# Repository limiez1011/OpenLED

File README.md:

# OpenLED

Open source ws2812 LED strips in 3 different size and connector configurations.

# Variants

There are 3 variants for the OpenLED:

- OpenLED LONG
- OpenLED WIDE
- OpenLED COMPACT

# Variant info and BOM's

## OpenLED LONG

- Dimensions: 44.2x7.1x7* (LxWxH)(mm) *Estimated

**BOM (per piece)**
|   | NAME                      | PURPOSE       | QTY | PRICE (MOQ)                  | LINK                                                      |
|---|---------------------------|---------------|-----|------------------------------|-----------------------------------------------------------|
| 1 | JST SM03B-SRSS-TB(LF)(SN) | JST Connector | 2   | $0.98                        | [LINK](https://www.lcsc.com/product-detail/C160403.html)  |
| 2 | Worldsemi WS2812B-V5/W    | LED'S         | 4   | $0.55                        | [LINK](https://www.lcsc.com/product-detail/C2874885.html) |
| 3 | YAGEO CC0402KRX7R9BB104   | Decoupling    | 4   | $0.5                         | [LINK](https://www.lcsc.com/product-detail/C131394.html)  |
|   | PCB                       | PCB           | 1   | Varies                       | [LINK](https://jlcpcb.com)                                |
|   | Total                     |               |     | $2.03 + PCB + SHIPPING/TAXES |                                                           |

- Photos

## OpenLED WIDE

- Dimensions: 40.1x8x7* (LxWxH)(mm) *Estimated

**BOM (per piece)**
|   | NAME                      | PURPOSE       | QTY | PRICE (MOQ)                  | LINK                                                      |
|---|---------------------------|---------------|-----|------------------------------|-----------------------------------------------------------|
| 1 | JST SM03B-SRSS-TB(LF)(SN) | JST Connector | 2   | $0.98                        | [LINK](https://www.lcsc.com/product-detail/C160403.html)  |
| 2 | Worldsemi WS2812B-V5/W    | LED'S         | 4   | $0.55                        | [LINK](https://www.lcsc.com/product-detail/C2874885.html) |
| 3 | YAGEO CC0402KRX7R9BB104   | Decoupling    | 4   | $0.5                         | [LINK](https://www.lcsc.com/product-detail/C131394.html)  |
|   | PCB                       | PCB           | 1   | Varies                       | [LINK](https://jlcpcb.com)                                |
|   | Total                     |               |     | $2.03 + PCB + SHIPPING/TAXES |                                                           |

- Photos

## OpenLED COMPACT

- Dimensions: 31.8x7.1x7* (LxWxH)(mm) *Estimated

**BOM (per piece)**
|   | NAME                      | PURPOSE       | QTY | PRICE (MOQ)                  | LINK                                                      |
|---|---------------------------|---------------|-----|------------------------------|-----------------------------------------------------------|
| 1 | Worldsemi WS2812B-V5/W    | LED'S         | 4   | $0.55                        | [LINK](https://www.lcsc.com/product-detail/C2874885.html) |
| 2 | YAGEO CC0402KRX7R9BB104   | Decoupling    | 4   | $0.5                         | [LINK](https://www.lcsc.com/product-detail/C131394.html)  |
|   | PCB                       | PCB           | 1   | Varies                       | [LINK](https://jlcpcb.com)                                |
|   | Total                     |               |     | $1.05 + PCB + SHIPPING/TAXES |                                                           |

- Photos

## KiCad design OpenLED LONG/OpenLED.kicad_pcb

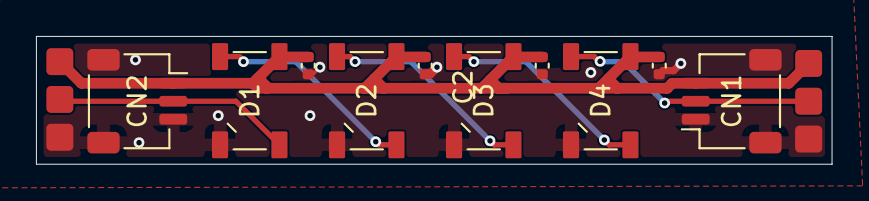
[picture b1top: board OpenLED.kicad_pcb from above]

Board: 2 copper layers, 44.2 x 7.1 mm, 10 parts (0 on the bottom side), 7 nets.

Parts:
C1, C2, C3, C4: 100nF; C_0402_1005Metric
CN1, CN2: SM03B-SRSS-TB; JST_SH_SM03B-SRSS-TB_1x03-1MP_P1.00mm_Horizontal
D1, D2, D3, D4: WS2812B; LED_WS2812B_PLCC4_5.0x5.0mm_P3.2mm

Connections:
+5V: C1.2, C2.2, C3.2, C4.2, CN1.3, CN2.1, D1.1 (VDD), D2.1 (VDD), D3.1 (VDD), D4.1 (VDD)
/DIN: CN2.2, D1.4 (DIN)
/DOUT: CN1.2, D4.2 (DOUT)
GND: C1.1, C2.1, C3.1, C4.1, CN1.1, CN1.MP, CN2.3, CN2.MP, D1.3 (VSS), D2.3 (VSS), D3.3 (VSS), D4.3 (VSS)
unnamed: D1.2 (DOUT), D2.4 (DIN)
unnamed: D2.2 (DOUT), D3.4 (DIN)
unnamed: D3.2 (DOUT), D4.4 (DIN)

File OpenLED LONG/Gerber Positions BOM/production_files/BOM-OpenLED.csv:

Comment,Designator,Footprint,LCSC,Quantity
100nF,"C1,C2,C3,C4",C_0402_1005Metric,C131394,4
SM03B-SRSS-TB,"CN1,CN2",JST_SH_SM03B-SRSS-TB_1x03-1MP_P1.00mm_Horizontal,C160403,2
WS2812B,"D1,D2,D3,D4",LED_WS2812B_PLCC4_5.0x5.0mm_P3.2mm,C2874885,4
